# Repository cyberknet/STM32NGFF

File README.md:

# STM32NGFF
# About
STM32 breakout board using NGFF card edge connector

For licensing information please see our LICENSE file

Created by the members of 33C (fka reindeer pig baboon with mouse accessory)

## Schematic

## PCB

## PCB 3D View
Front:

Back:

Traces

# Contact
Join us on Discord at https://discord.gg/E6ujkUG

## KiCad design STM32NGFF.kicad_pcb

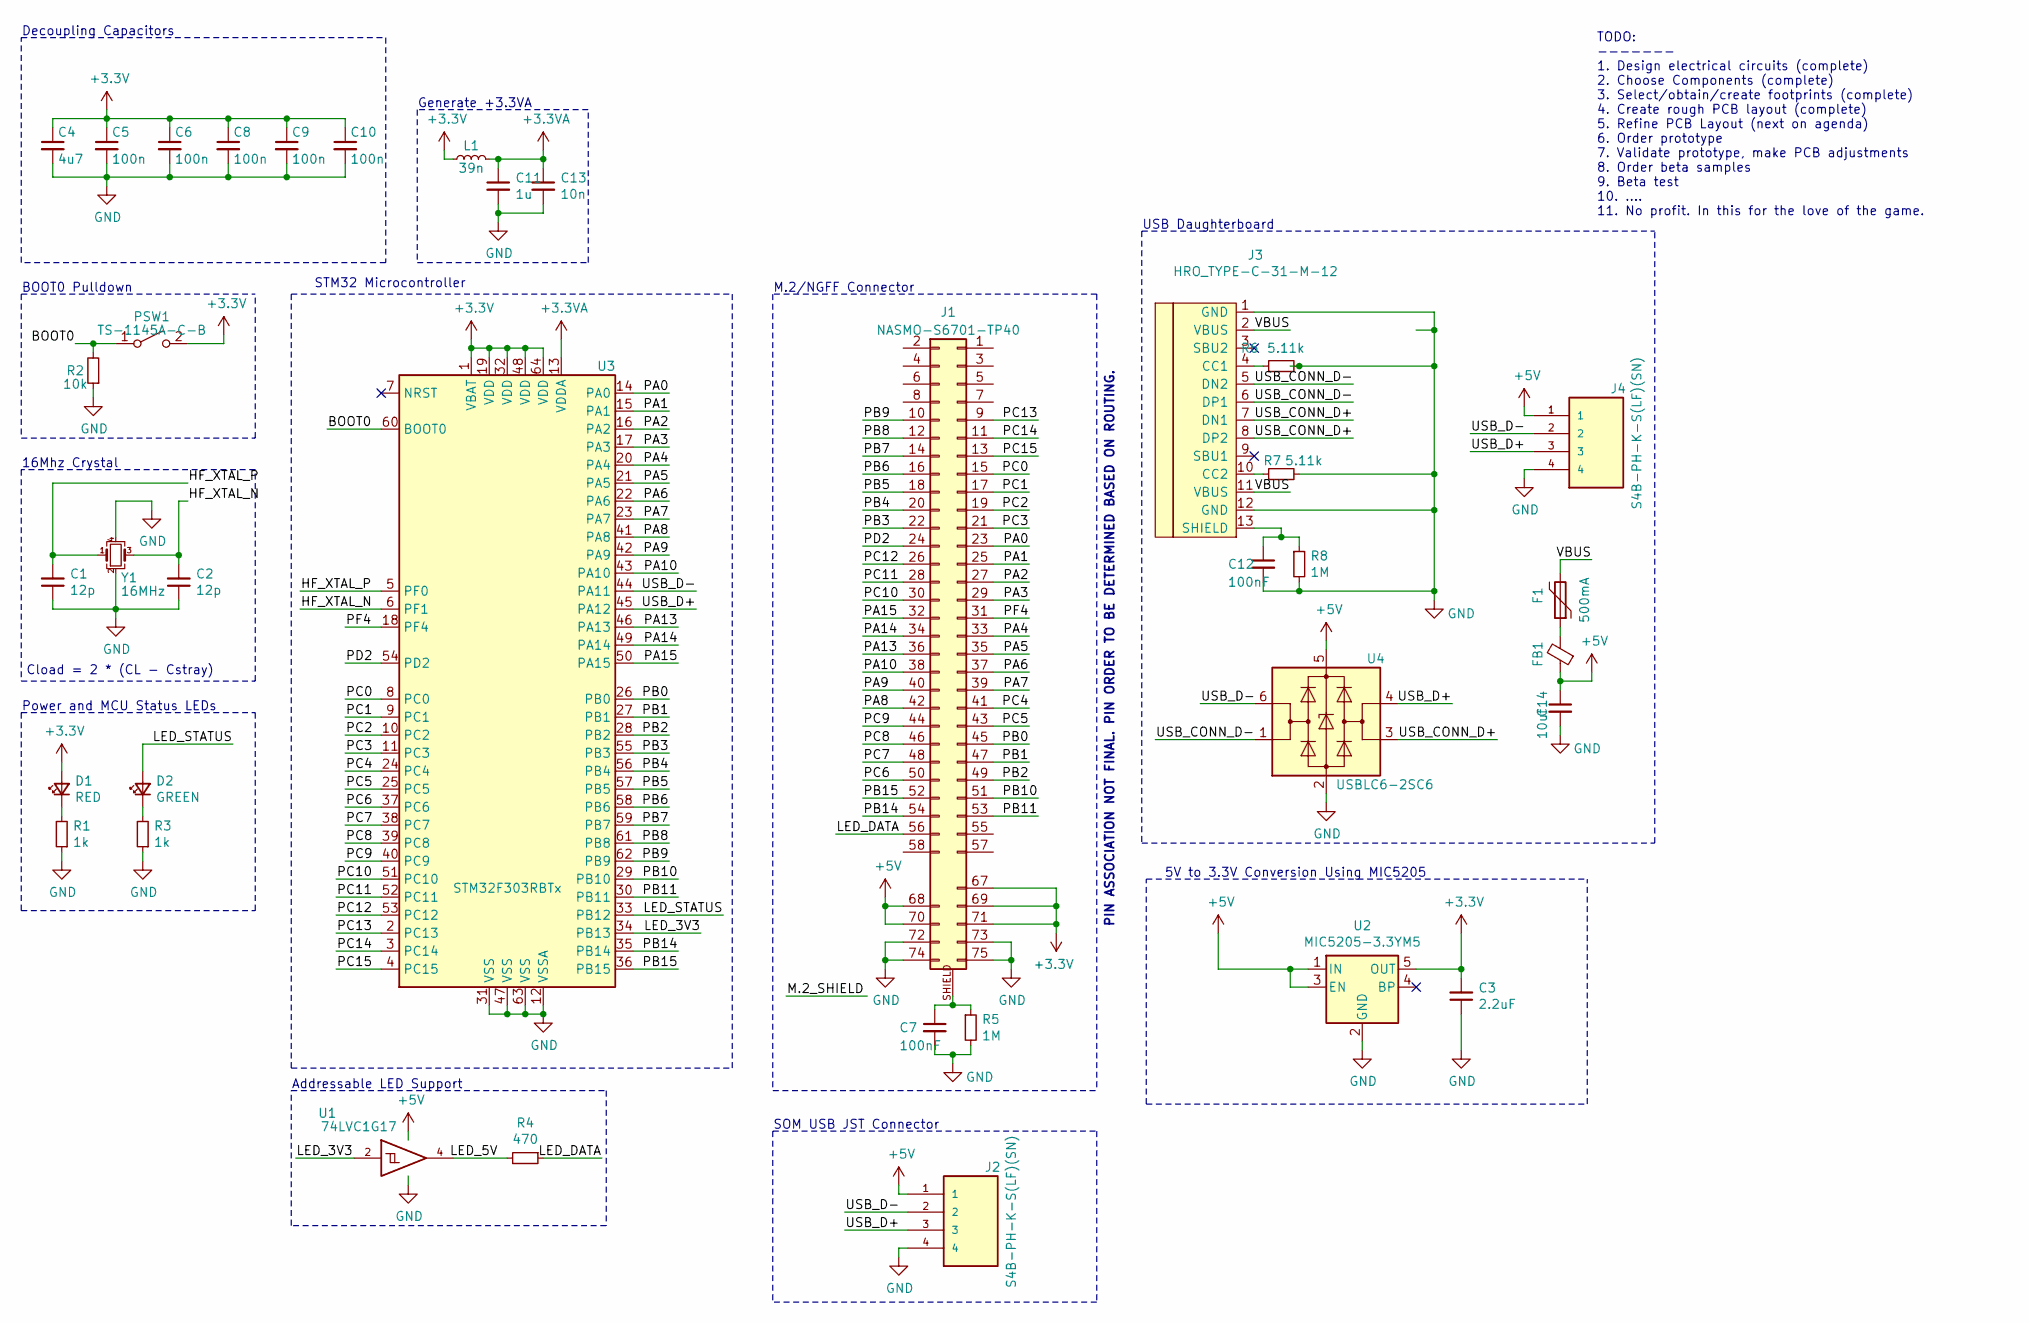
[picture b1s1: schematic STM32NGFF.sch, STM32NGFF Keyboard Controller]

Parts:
C1, C2: 12p; C_0603_1608Metric
C3: 2.2uF; C_0603_1608Metric
C4: 4u7; C_0603_1608Metric
C5, C6, C8, C9, C10: 100n; C_0603_1608Metric
C7, C12: 100nF; C_0603_1608Metric
C11: 1u; C_0603_1608Metric
C13: 10n; C_0603_1608Metric
C14: 10uf; C_0603_1608Metric
D1: RED; LED_0201_0603Metric_Castellated
D2: GREEN; LED_0201_0603Metric_Castellated
F1: 500mA; Fuse_0805_2012Metric_Castellated
FB1: Fuse_0805_2012Metric
J1: NASMO-S6701-TP40
J2, J4: S4B-PH-K-S(LF)(SN); S4B-PH-K-S_LF_SN
J3: HRO_TYPE-C-31-M-12; HRO-TYPE-C-31-M-12-Assembly
L1: 39n; L_0603_1608Metric
PSW1: TS-1145A-C-B; SW_SPST_PTS810
R1, R3: 1k; C_0603_1608Metric
R2: 10k; C_0603_1608Metric
R4: 470; C_0603_1608Metric
R5, R8: 1M; C_0603_1608Metric
R6, R7: 5.11k; C_0603_1608Metric
U1: 74LVC1G17; SOT-23-5
U2: MIC5205-3.3YM5; SOT-23-5
U3: STM32F303RBTx; LQFP-64_10x10mm_P0.5mm
U4: USBLC6-2SC6; SOT-23-6
Y1: 16MHz; Crystal_SMD_3225-4Pin_3.2x2.5mm

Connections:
+3.3VA: C11.1, C13.1, L1.2, U3.13 (VDDA)
+3V3: C3.2, C4.1, C5.1, C6.1, C8.1, C9.1, C10.1, D1.2 (A), J1.67, J1.69, J1.71, L1.1, PSW1.2 (B), U2.5 (OUT), U3.1 (VBAT), U3.19 (VDD), U3.32 (VDD), U3.48 (VDD), U3.64 (VDD)
+5V: C14.1, FB1.1, J1.68, J1.70, J2.1, J4.1, U1.5 (VCC), U2.1 (IN), U2.3 (EN), U4.5 (VBUS)
/BOOT0: PSW1.1 (A), R2.2, U3.60 (BOOT0)
/HF_XTAL_N: C2.2, U3.6 (PF1), Y1.3
/HF_XTAL_P: C1.2, U3.5 (PF0), Y1.1
/LED_3V3: U1.2, U3.34 (PB13)
/LED_5V: R4.2, U1.4
/LED_DATA: J1.56, R4.1
/LED_STATUS: D2.2 (A), U3.33 (PB12)
/PA0: J1.23, U3.14 (PA0)
/PA1: J1.25, U3.15 (PA1)
/PA2: J1.27, U3.16 (PA2)
/PA3: J1.29, U3.17 (PA3)
/PA4: J1.33, U3.20 (PA4)
/PA5: J1.35, U3.21 (PA5)
/PA6: J1.37, U3.22 (PA6)
/PA7: J1.39, U3.23 (PA7)
/PA8: J1.42, U3.41 (PA8)
/PA9: J1.40, U3.42 (PA9)
/PA10: J1.38, U3.43 (PA10)
/PA13: J1.36, U3.46 (PA13)
/PA14: J1.34, U3.49 (PA14)
/PA15: J1.32, U3.50 (PA15)
/PB0: J1.45, U3.26 (PB0)
/PB1: J1.47, U3.27 (PB1)
/PB2: J1.49, U3.28 (PB2)
/PB3: J1.22, U3.55 (PB3)
/PB4: J1.20, U3.56 (PB4)
/PB5: J1.18, U3.57 (PB5)
/PB6: J1.16, U3.58 (PB6)
/PB7: J1.14, U3.59 (PB7)
/PB8: J1.12, U3.61 (PB8)
/PB9: J1.10, U3.62 (PB9)
/PB10: J1.51, U3.29 (PB10)
/PB11: J1.53, U3.30 (PB11)
/PB14: J1.54, U3.35 (PB14)
/PB15: J1.52, U3.36 (PB15)
/PC0: J1.15, U3.8 (PC0)
/PC1: J1.17, U3.9 (PC1)
/PC2: J1.19, U3.10 (PC2)
/PC3: J1.21, U3.11 (PC3)
/PC4: J1.41, U3.24 (PC4)
/PC5: J1.43, U3.25 (PC5)
/PC6: J1.50, U3.37 (PC6)
/PC7: J1.48, U3.38 (PC7)
/PC8: J1.46, U3.39 (PC8)
/PC9: J1.44, U3.40 (PC9)
/PC10: J1.30, U3.51 (PC10)
/PC11: J1.28, U3.52 (PC11)
/PC12: J1.26, U3.53 (PC12)
/PC13: J1.9, U3.2 (PC13)
/PC14: J1.11, U3.3 (PC14)
/PC15: J1.13, U3.4 (PC15)
/PD2: J1.24, U3.54 (PD2)
/PF4: J1.31, U3.18 (PF4)
/USB_CONN_D+: J3.7 (DN1), J3.8 (DP2), U4.3 (I/O2)
/USB_CONN_D-: J3.5 (DN2), J3.6 (DP1), U4.1 (I/O1)
/USB_D+: J2.3, J4.3, U3.45 (PA12), U4.4 (I/O2)
/USB_D-: J2.2, J4.2, U3.44 (PA11), U4.6 (I/O1)
/VBUS: F1.2, J3.2 (VBUS), J3.11 (VBUS)
GND: C1.1, C2.1, C3.1, C4.2, C5.2, C6.2, C7.2, C8.2, C9.2, C10.2, C11.2, C12.2, C13.2, C14.2, J1.72, J1.73, J1.74, J1.75, J2.4, J3.1 (GND), J3.12 (GND), J4.4, R1.1, R2.1, R3.1, R5.2, R6.2, R7.2, R8.2, U1.3 (GND), U2.2 (GND), U3.12 (VSSA), U3.31 (VSS), U3.47 (VSS), U3.63 (VSS), U4.2 (GND), Y1.2, Y1.4
unnamed: C7.1, J1.SHIELD, R5.1
unnamed: C12.1, J3.13 (SHIELD), R8.1
unnamed: D1.1 (K), R1.2
unnamed: D2.1 (K), R3.2
unnamed: F1.1, FB1.2
unnamed: J3.4 (CC1), R6.1
unnamed: J3.10 (CC2), R7.1

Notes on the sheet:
Cload = 2 * (CL - Cstray)
STM32 Microcontroller
Power and MCU Status LEDs
USB Daughterboard
M.2/NGFF Connector
Decoupling Capacitors
16Mhz Crystal
Generate +3.3VA
BOOT0 Pulldown
TODO: ------- 1. Design electrical circuits (complete) 2. Choose Components (complete) 3. Select/obtain/create footprints (complete) 4. Create rough PCB layout (complete) 5. Refine PCB Layout (next on agenda) 6. Order prototype 7. Validate prototype, make PCB adjustments 8. Order beta samples 9. Be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
5V to 3.3V Conversion Using MIC5205
PIN ASSOCIATION NOT FINAL. PIN ORDER TO BE DETERMINED BASED ON ROUTING.
Addressable LED Support
SOM USB JST Connector

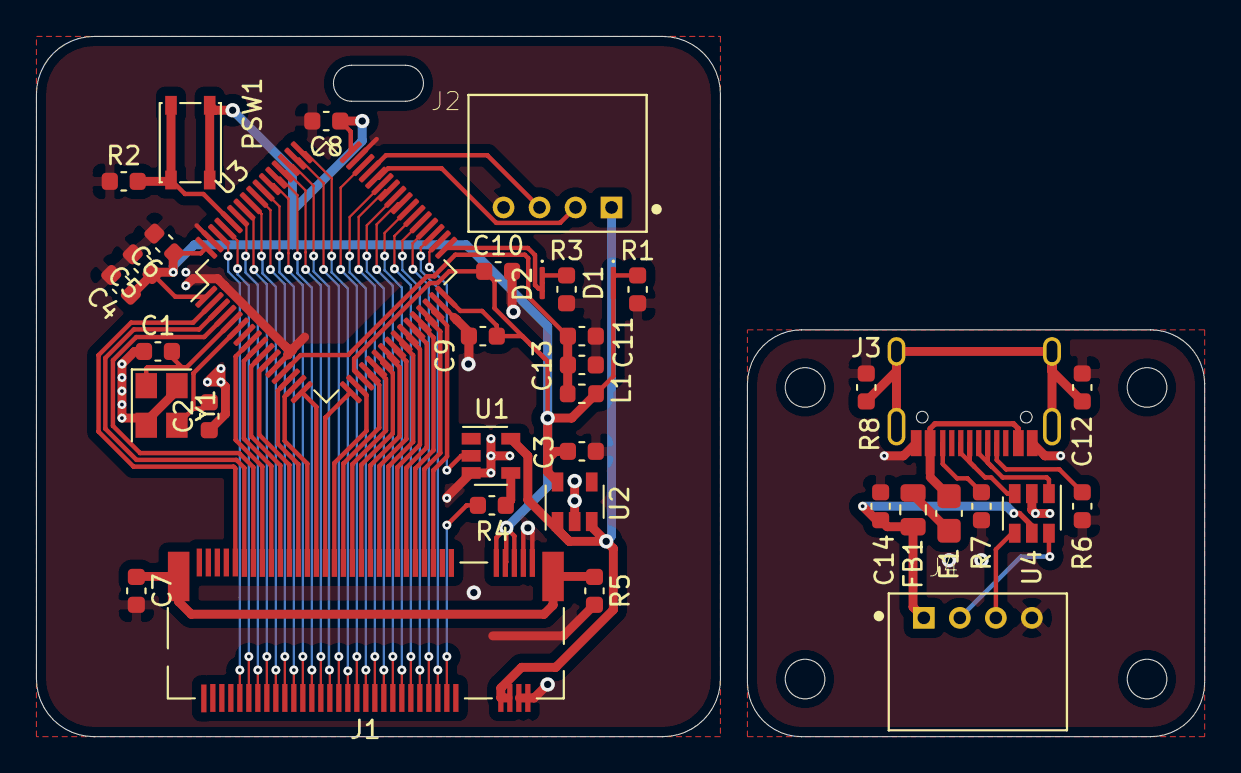
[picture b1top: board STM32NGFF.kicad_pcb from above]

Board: 2 copper layers, 64.9 x 38.9 mm, 37 parts (0 on the bottom side), 69 nets.

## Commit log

2020-11-13 Added initial schematic
2020-11-13 added github repo to schematic and PCB
2020-11-13 Added LM117 implementation of 5V to 3.3V conversion
2020-11-13 Updated to built-in USB symbol and organized schematic
2020-11-13 Removed blank PCB and updated schematic with Discord info
2020-11-13 Updated README with Discord info
2020-11-13 Updated 3.3V generation to MIC5205
2020-11-13 Finalized schematic and started PCB
2020-11-13 Updated schematic in VC, ready for initial PCB
2020-11-13 Removing backup files
2020-11-13 Added initial PCB, and updated all global labels to net labels
2020-11-13 Updated page titles
2020-11-14 Add Correct M.2 Connector, and switch MCU to STM32F303RBTx
2020-11-18 Routed and shaped PCB
2020-11-18 Updated TODO list in schematic
2020-11-18 Updated images
2020-11-18 Added images to the README
2020-11-18 corrected README heading
2020-11-22 Updated 3.3V Generator and NGFF footprint
2020-11-22 Updated NGFF pinout for 3.3V, 5V, and GND
2020-11-22 Added PCB back view, and chipless view of front
2020-11-22 Updated README.md to include new board views

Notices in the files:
STM32NGFF.kicad_pcb:
CERN Open Hardware License - Strongly Reciprocal V2
